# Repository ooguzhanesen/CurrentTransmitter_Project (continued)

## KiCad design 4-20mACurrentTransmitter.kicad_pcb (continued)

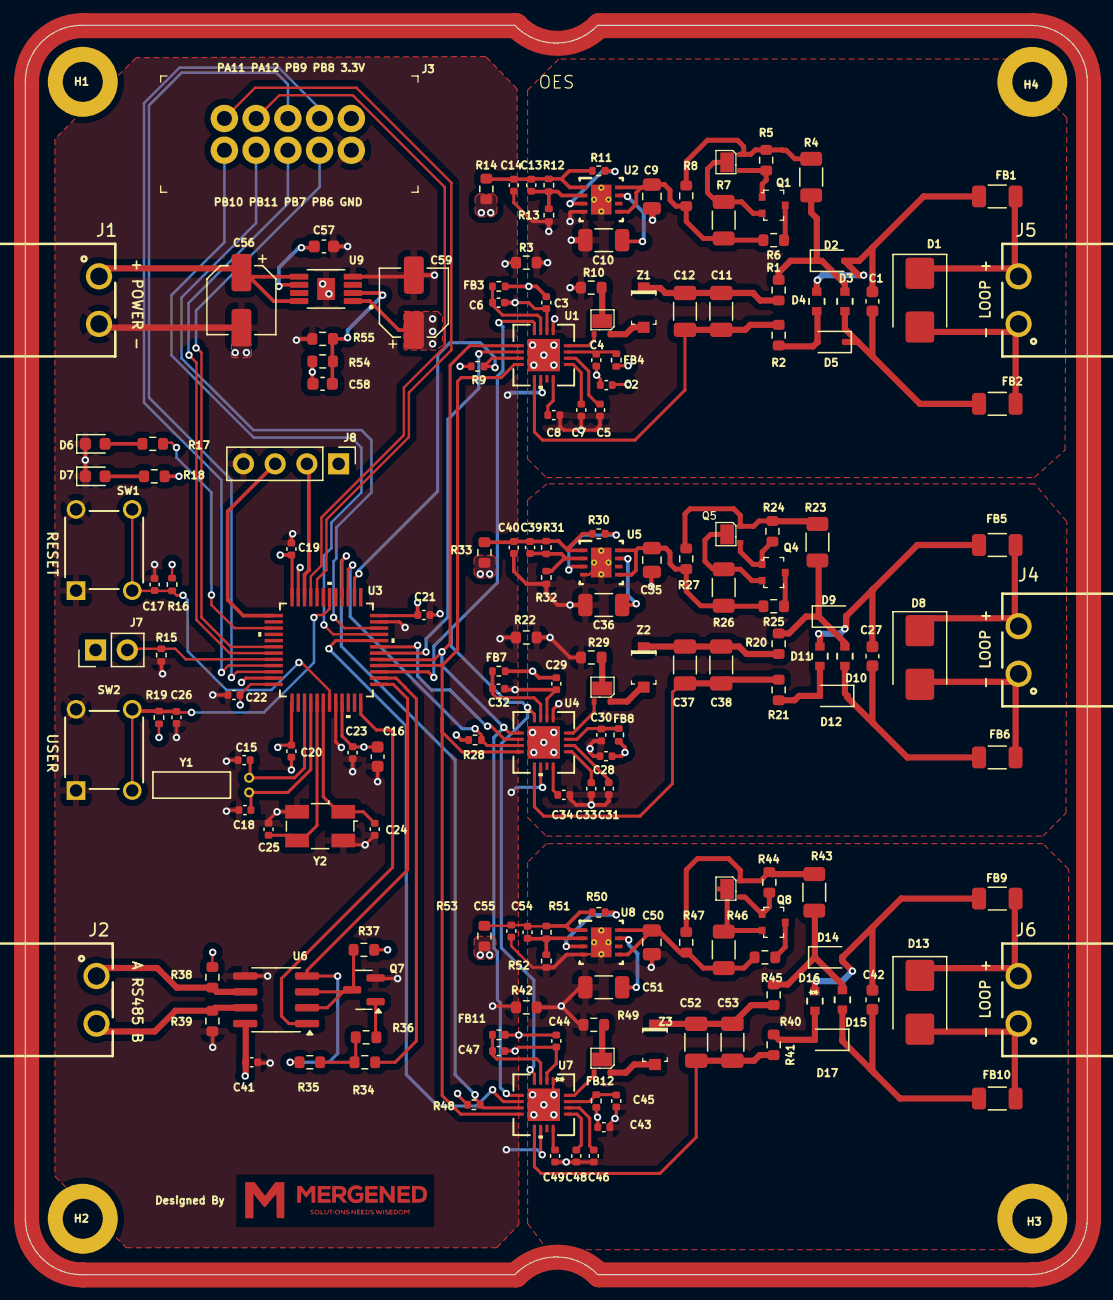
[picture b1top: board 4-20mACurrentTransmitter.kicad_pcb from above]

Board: 4 copper layers, 85.0 x 100.0 mm, 181 parts (0 on the bottom side), 123 nets.

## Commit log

2025-01-04 fixed readme
